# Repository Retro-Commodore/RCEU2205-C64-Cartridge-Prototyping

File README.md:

# RCEU2205 - C64 Cartridge Prototyping
A prototyping cartridge with cart connectors and/or header pins

With this you can add cartridge edge connectors and/or header pins, quite useful for doing diagnostics or other kinds of fun with the Commodore 64/128 cartridge port.

Component list, recommended but not required
* DIL/SIL headers 2.54mm pitch
* 44pin Edge connector 2.54mm pitch, vertical and/or horizontal

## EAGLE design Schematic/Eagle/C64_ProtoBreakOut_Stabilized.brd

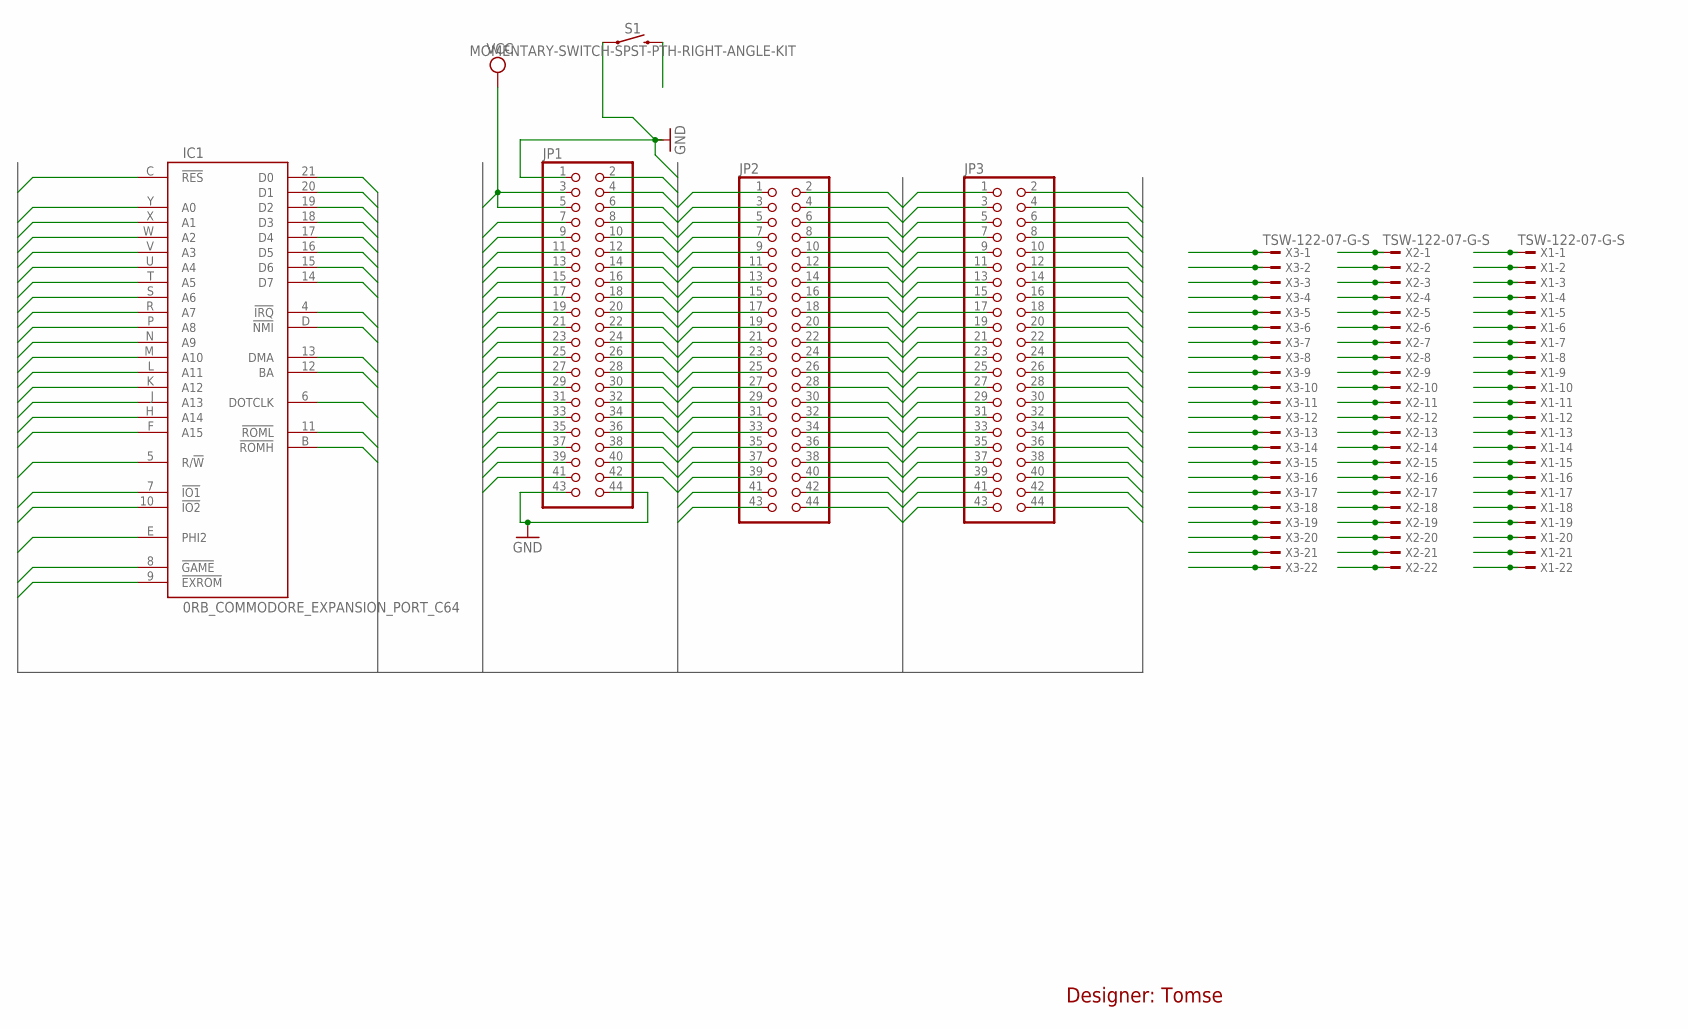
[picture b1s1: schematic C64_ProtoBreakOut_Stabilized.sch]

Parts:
IC1: 0RB_COMMODORE_EXPANSION_PORT_C64; 0RB_COMMODORE_MA100-22-2
JP1, JP2, JP3: PINHD-2X22; 2X22
S1: MOMENTARY-SWITCH-SPST-PTH-RIGHT-ANGLE-KIT; TACTILE_SWITCH_PTH_RIGHT_ANGLE_KIT
X1, X2, X3: TSW-122-07-G-S; TSW-122-XX-G-S

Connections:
!DMA: IC1.13 (DMA), JP1.25, JP2.25, JP3.25, X1.13, X2.13, X3.13
!EXROM: IC1.9 (!EXROM), JP1.17, JP2.17, JP3.17, X1.9, X2.9, X3.9
!GAME: IC1.8 (!GAME), JP1.15, JP2.15, JP3.15, X1.8, X2.8, X3.8
!IO1: IC1.7 (!IO1), JP1.13, JP2.13, JP3.13, X1.7, X2.7, X3.7
!IO2: IC1.10 (!IO2), JP1.19, JP2.19, JP3.19, X1.10, X2.10, X3.10
!IRQ: IC1.4 (!IRQ), JP1.7, JP2.7, JP3.7, X1.4, X2.4, X3.4
!NMI: IC1.D (!NMI), JP1.8, JP2.8, JP3.8
!RES: IC1.C (!RES), JP1.6, JP2.6, JP3.6, S1.2
!ROMH: IC1.B (!ROMH), JP1.4, JP2.4, JP3.4
!ROML: IC1.11 (!ROML), JP1.21, JP2.21, JP3.21, X1.11, X2.11, X3.11
A0: IC1.Y (A0), JP1.42, JP2.42, JP3.42
A1: IC1.X (A1), JP1.40, JP2.40, JP3.40
A2: IC1.W (A2), JP1.38, JP2.38, JP3.38
A3: IC1.V (A3), JP1.36, JP2.36, JP3.36
A4: IC1.U (A4), JP1.34, JP2.34, JP3.34
A5: IC1.T (A5), JP1.32, JP2.32, JP3.32
A6: IC1.S (A6), JP1.30, JP2.30, JP3.30
A7: IC1.R (A7), JP1.28, JP2.28, JP3.28
A8: IC1.P (A8), JP1.26, JP2.26, JP3.26
A9: IC1.N (A9), JP1.24, JP2.24, JP3.24
A10: IC1.M (A10), JP1.22, JP2.22, JP3.22
A11: IC1.L (A11), JP1.20, JP2.20, JP3.20
A12: IC1.K (A12), JP1.18, JP2.18, JP3.18
A13: IC1.J (A13), JP1.16, JP2.16, JP3.16
A14: IC1.H (A14), JP1.14, JP2.14, JP3.14
A15: IC1.F (A15), JP1.12, JP2.12, JP3.12
BA: IC1.12 (BA), JP1.23, JP2.23, JP3.23, X1.12, X2.12, X3.12
D0: IC1.21 (D0), JP1.41, JP2.41, JP3.41, X1.21, X2.21, X3.21
D1: IC1.20 (D1), JP1.39, JP2.39, JP3.39, X1.20, X2.20, X3.20
D2: IC1.19 (D2), JP1.37, JP2.37, JP3.37, X1.19, X2.19, X3.19
D3: IC1.18 (D3), JP1.35, JP2.35, JP3.35, X1.18, X2.18, X3.18
D4: IC1.17 (D4), JP1.33, JP2.33, JP3.33, X1.17, X2.17, X3.17
D5: IC1.16 (D5), JP1.31, JP2.31, JP3.31, X1.16, X2.16, X3.16
D6: IC1.15 (D6), JP1.29, JP2.29, JP3.29, X1.15, X2.15, X3.15
D7: IC1.14 (D7), JP1.27, JP2.27, JP3.27, X1.14, X2.14, X3.14
DOTCLK: IC1.6 (DOTCLK), JP1.11, JP2.11, JP3.11, X1.6, X2.6, X3.6
GND: IC1.1 (GND), IC1.22 (GND), IC1.A (GND), IC1.Z (GND), JP1.1, JP1.2, JP1.43, JP1.44, JP2.1, JP2.2, JP2.43, JP2.44, JP3.1, JP3.2, JP3.43, JP3.44, S1.1, X1.1, X1.22, X2.1, X2.22, X3.1, X3.22
PHI2: IC1.E (PHI2), JP1.10, JP2.10, JP3.10
R!W: IC1.5 (R/!W), JP1.9, JP2.9, JP3.9, X1.5, X2.5, X3.5
VCC: IC1.2 (VCC), IC1.3 (VCC), JP1.3, JP1.5, JP2.3, JP2.5, JP3.3, JP3.5, X1.2, X1.3, X2.2, X2.3, X3.2, X3.3

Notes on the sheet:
Designer: Tomse

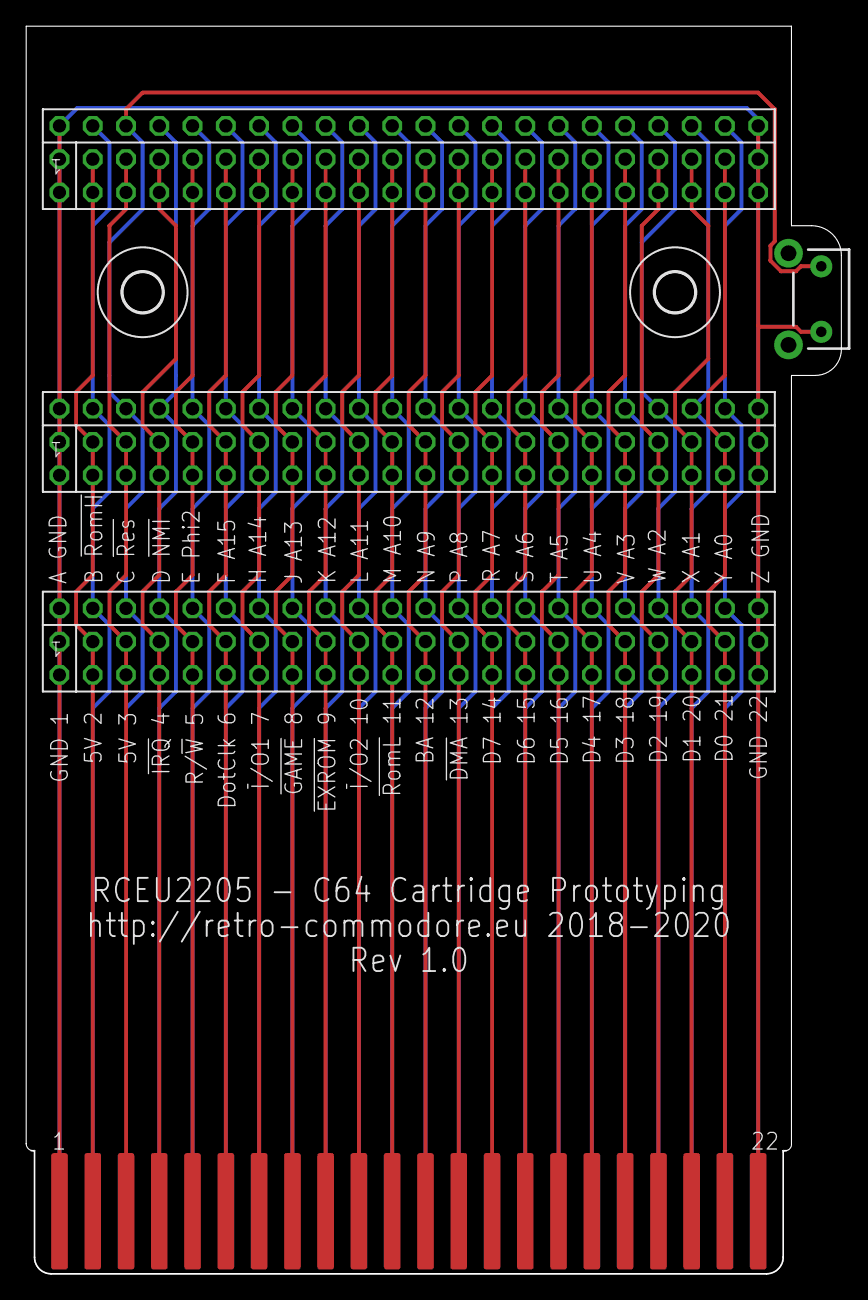
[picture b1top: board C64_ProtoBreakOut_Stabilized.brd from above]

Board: 2 copper layers, 62.2 x 95.2 mm, 10 parts (0 on the bottom side), 40 nets.

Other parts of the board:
U$1, U$2: 3,0

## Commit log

2019-01-02 Create bottom.jpg
    added more pics
2019-01-02 Create top.jpg
    added more pics
2020-04-06 Fixing dirnaming
2020-04-06 Cosmetic changes

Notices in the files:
Schematic/Eagle/C64_ProtoBreakOut_Stabilized.sch:
DESIGNER: Copyright (c) 2018 http://retro-commodore.eu
parts and their libraries:
SparkFun-Switches: Licensing: Creative Commons ShareAlike 4.0 International - https://creativecommons.org/licenses/by-sa/4.0
